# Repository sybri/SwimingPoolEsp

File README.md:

# SwimingPoolEsp
Swiming pool regulator

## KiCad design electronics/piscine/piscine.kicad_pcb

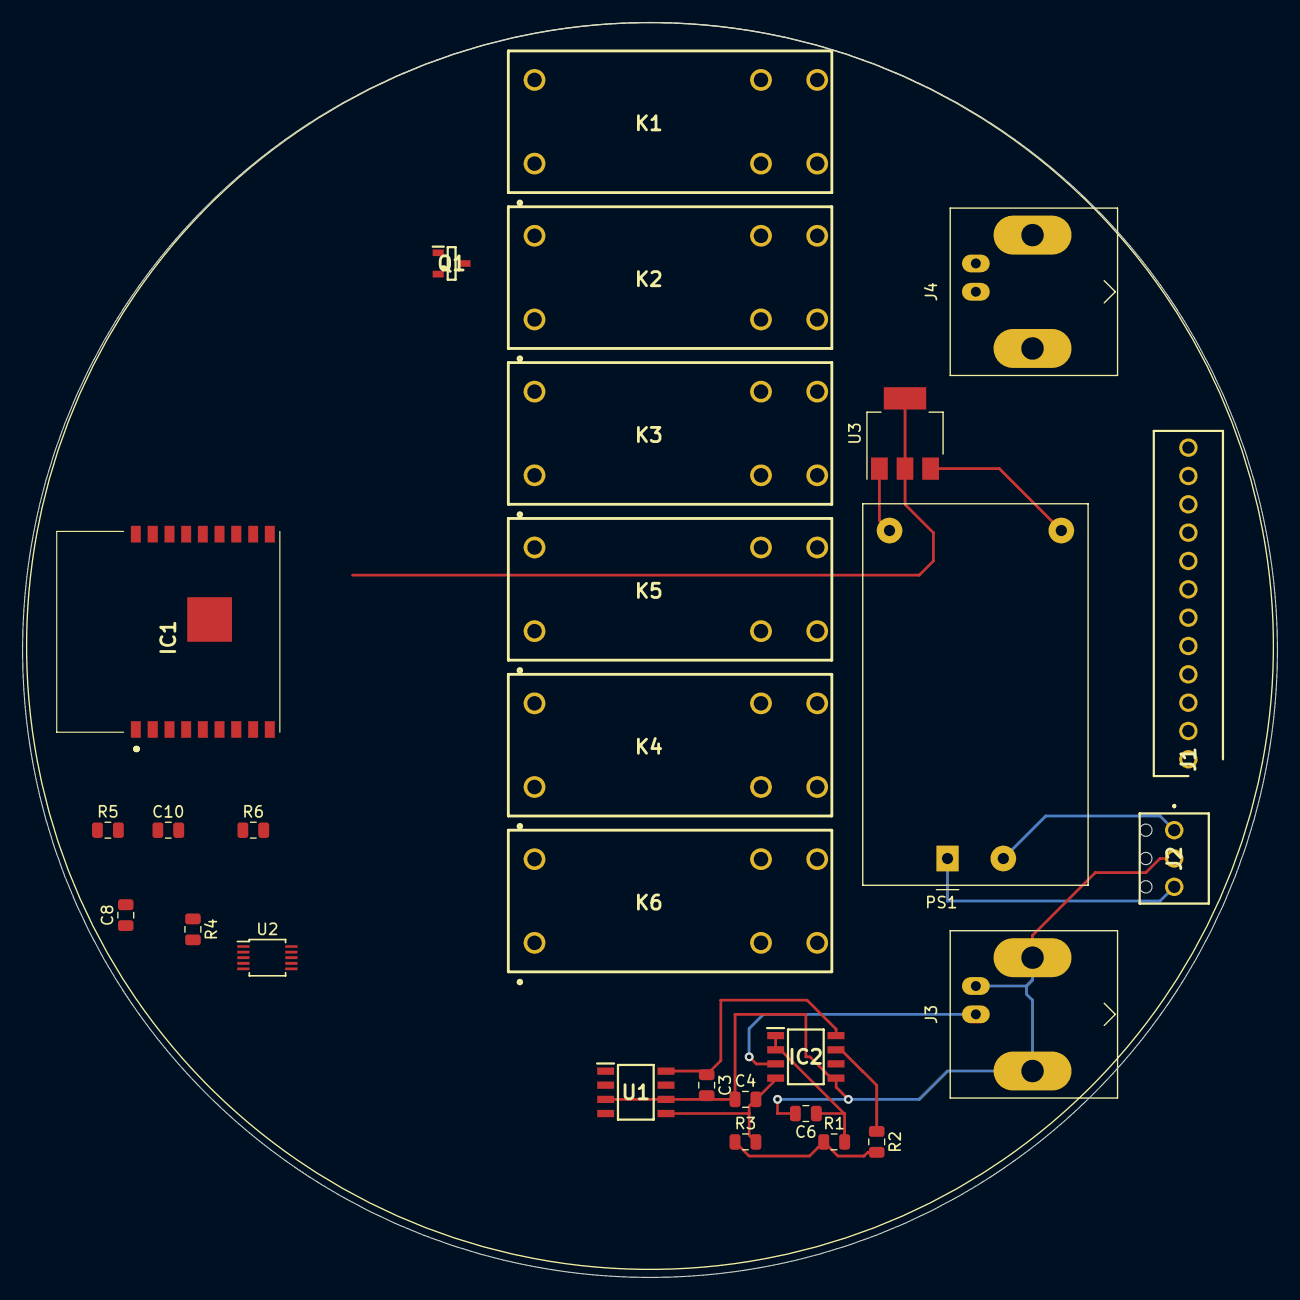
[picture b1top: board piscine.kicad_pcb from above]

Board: 2 copper layers, 112.5 x 112.5 mm, 28 parts (0 on the bottom side), 16 nets.

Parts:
C3, C6, C8, C10: C; C_0805_2012Metric
C4: 0.1uF; C_0805_2012Metric
IC1: ESP-WROOM-02_(4MB); ESPWROOM024MB
IC2: TL032CD; SOIC127P600X175-8N
J1: 1725753; SHDR12W90P0X254_1X12_3094X620X850P
J2: 1725669
J3, J4: Conn_Coaxial; BNC_Amphenol_B6252HB-NPP3G-50_Horizontal
K1, K2, K3, K4, K5, K6: RZ03-1A4-D005; RZ03-1A4
PS1: HLK-PM01; Converter_ACDC_HiLink_HLK-PMxx
Q1: MDC3105LT1G; SOT96P237X111-3N
R1, R2, R3, R5, R6: R; R_0805_2012Metric
R4: 0R; R_0805_2012Metric
U1: LM2662M_NOPB; SOIC127P600X175-8N
U2: ADS1115IDGS; TSSOP-10_3x3mm_P0.5mm
U3: LD1117S33TR_SOT223; SOT-223-3_TabPin2

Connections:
+3V3: C8.1, R5.2, U3.2
+5V: C3.1, IC2.8, K1.6, PS1.4, U1.8, U2.8, U3.3
-5V: C4.2, IC2.4, R3.2, U1.5
GND: C3.2, C4.1, C6.2, C8.2, C10.2, IC1.9, IC1.18, IC1.19, IC2.5, J2.2, J3.2, PS1.3, Q1.2, R4.2, R6.2, U1.3, U1.6, U2.3, U3.1
unnamed: C6.1, IC2.1, IC2.2, R1.2
unnamed: C10.1, IC1.2, R5.1
unnamed: IC1.6, R6.1
unnamed: IC2.3, J3.1
unnamed: IC2.6, R1.1, R2.2, R3.1
unnamed: J2.1, PS1.2
unnamed: J2.3, PS1.1
unnamed: K1.1, Q1.3
unnamed: R4.1, U2.1
ORP: IC2.7, R2.1, U2.4
scl: IC1.3, U2.10
sda: IC1.7, U2.9
